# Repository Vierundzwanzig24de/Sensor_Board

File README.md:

# Sensor Board V1

## Platine in Betrieb nehmen:
1. Keine Fuses einlöten, reverse polarity testen (Q1201)
	- Q1201 Pin 3 liegt Versorgungsspannung an
	- V_IN LED (D1210) leuchtet
	- F_Vdrive einlöten, Vdrive LED (D1206) leuchtet
2. Buck converter:
	- F_BUCK (F1201) einlöten
	- U1201 Pin 1 liegen 6V an
	- U1202 Pin 2 liegen 5V an
	- U1203 Pin 2 liegen 5V an
3. LDOs:
	- F_5VA, F_5V und F_3V3 nacheinander einlöten und Ausgänge testen
	- 5VA, 5V und 3.3V LEDs leuchten auf
	- Versorgung wegnehmen und F_USB einlöten
	- USB Versorgung anschließen
	- V_IN, Vdrive und 5VA LEDs bleiben aus, 5V und 3.3V leuchten
	- USB Jumper links setzen (Pins 2+3), 5VA LED leuchtet
	- Spannung an U1203 Pin 2 ist ~0V
	- USB Jumper alle Pins verbinden
	- Spannung an U1202 Pin 2 ist ~0V
	- Eingangsspannung verbinden, V_IN und Vdrive leuchten, Stromverbrauch normal
	- Spannung über D1204 und D1205 messen, danach USB Jumper rechts setzen (Pins 1+2)
	- USB Versorgung trennen, Ausgangsspannung U1202 vergleichen zwischen USB und ohne -> D1204 überbrücken? Wenn ja, Jumper USB nur noch wechseln zwischen 1/2 und 2/3
4. STM32:
	- ST-Link verbinden und Testprogramm aufspielen
	- STATUS LED blinkt
	- Versorgungsspannung wegnehmen
	- USB Versorgung verbinden und erneut Testprogramm aufspielen
	- STATUS LED blinkt immer noch
	
## Prüfen:
- 74HC595 Ausgangsspannung an PU/PD Widerständen!
- Flankensteilheit Halbbrücken einstellen

## Für V2:
- Halbbrücken näher an Stecker (Halbbrücken, 1A-Profets, Buck converter)
- STM um 90° drehen
- USB Stecker weiter herausstehen lassen
- kleinere Gehäuse für ICs nutzen
- Level shifter für 74HC595 nicht notwendig
- 3.3V Outputs??
- Umschalten Ausgangsspannung per Software
- Umschalten USB Versorgung per Software?? (Falls keine Eingangsspannung messbar)
- CAN schaltbare Terminierung
- Vierundzwanzig24 Logo!!!
- AMPSEAL um 0.8mm (0.7mm?) nach innen verschieben

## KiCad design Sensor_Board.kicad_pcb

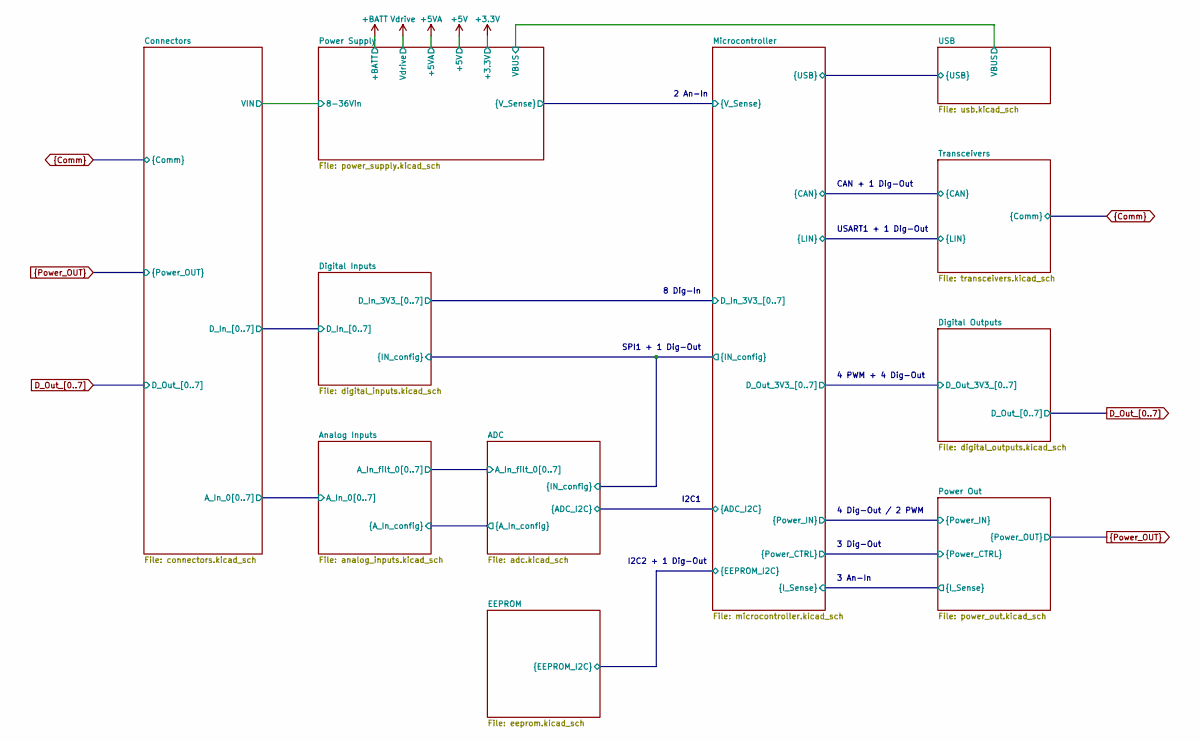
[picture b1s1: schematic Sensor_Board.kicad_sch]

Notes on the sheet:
I2C1
SPI1 + 1 Dig-Out
3 An-In
CAN + 1 Dig-Out
4 Dig-Out / 2 PWM
USART1 + 1 Dig-Out
I2C2 + 1 Dig-Out
3 Dig-Out
4 PWM + 4 Dig-Out
8 Dig-In
2 An-In

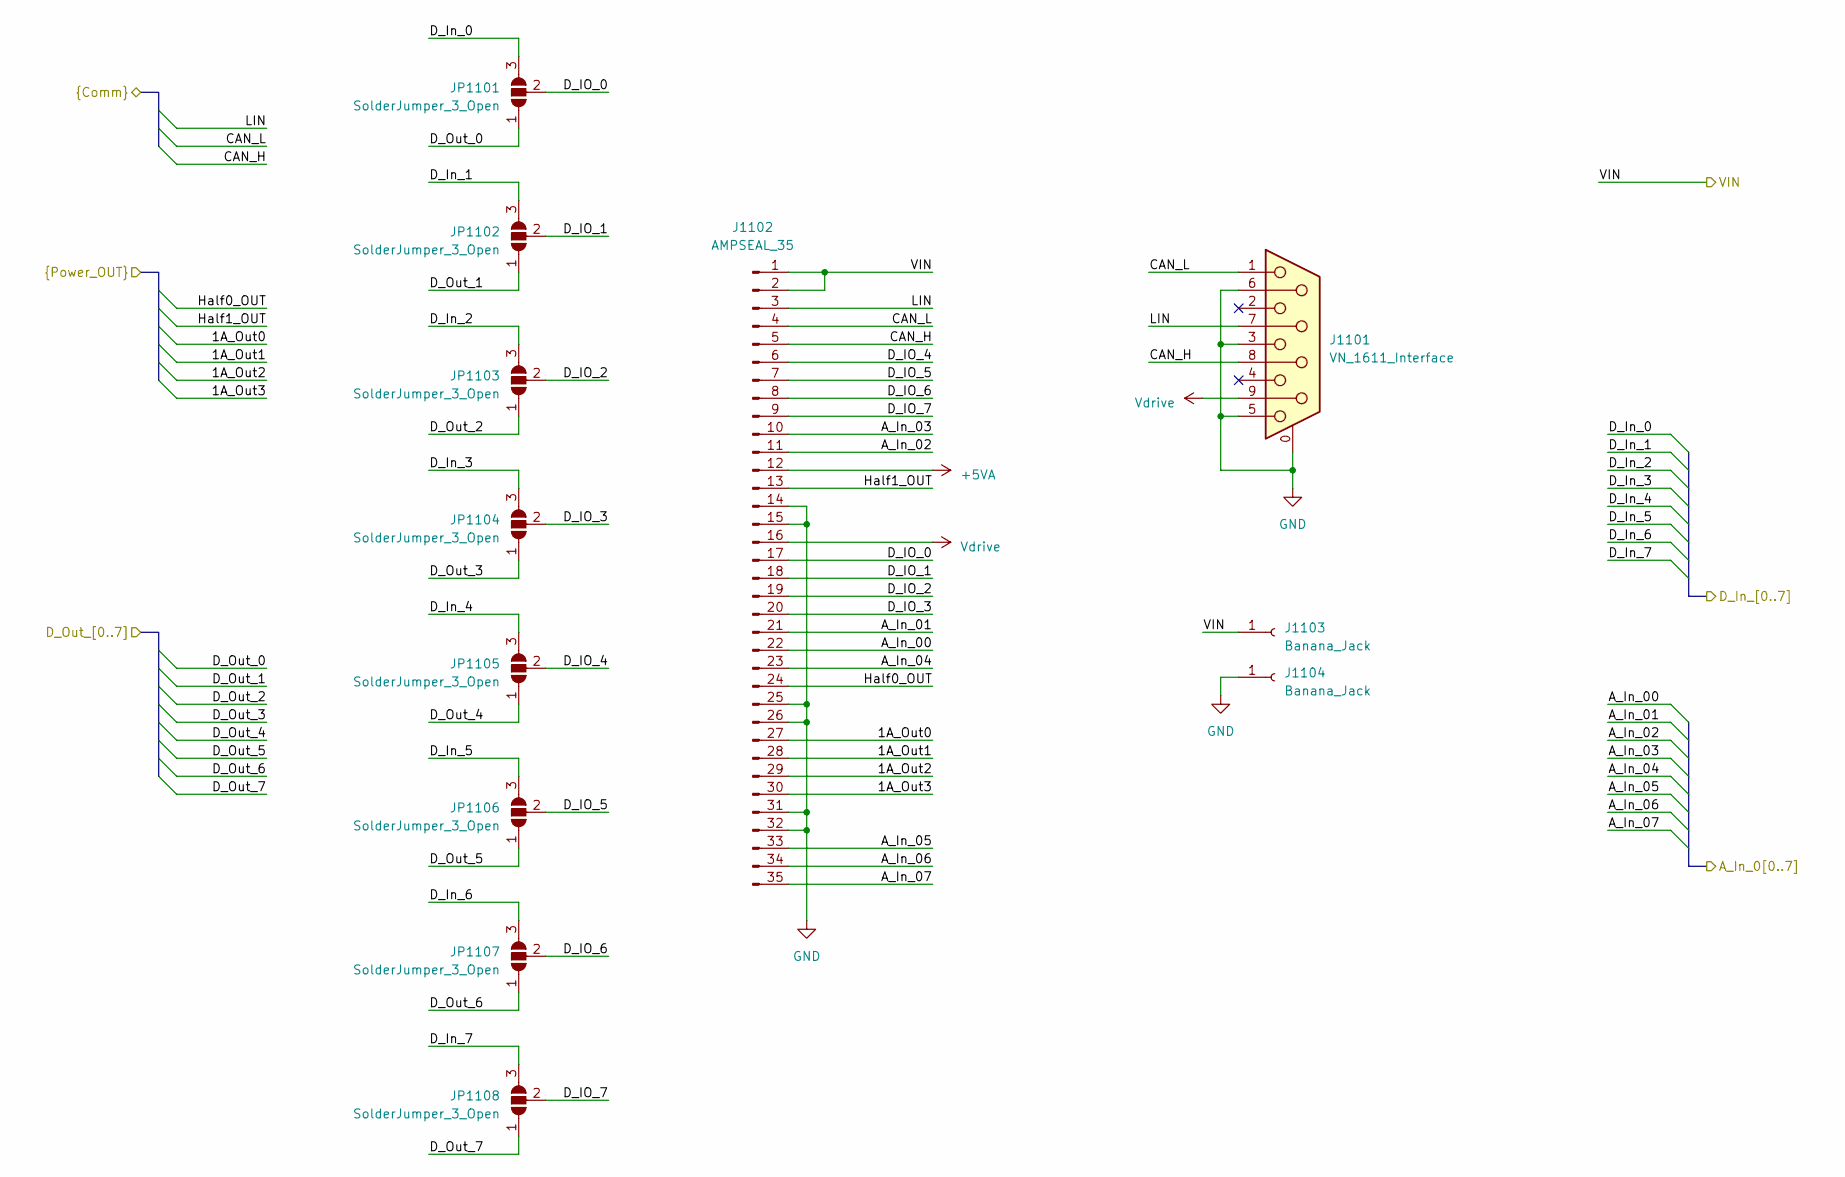
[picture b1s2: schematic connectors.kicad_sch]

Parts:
J1101: VN_1611_Interface; DSUB-9_Female_Horizontal_P2.77x2.84mm_EdgePinOffset9.90mm_H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
J1102: AMPSEAL_35
J1103, J1104: Banana_Jack; Banana_Cliff_FCR7350x_S16N-PC_Horizontal
JP1101, JP1102, JP1103, JP1104, JP1105, JP1106, JP1107, JP1108: SolderJumper_3_Open; SolderJumper-3_P1.3mm_Open_Pad1.0x1.5mm

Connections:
1A_Out1: J1102.28; also elsewhere on the board
1A_Out2: J1102.29; also elsewhere on the board
+5VA: J1102.12; also elsewhere on the board
/Analog Inputs/A_In_00: J1102.22; also elsewhere on the board
/Analog Inputs/A_In_01: J1102.21; also elsewhere on the board
/Analog Inputs/A_In_02: J1102.11; also elsewhere on the board
/Analog Inputs/A_In_03: J1102.10; also elsewhere on the board
/Analog Inputs/A_In_04: J1102.23; also elsewhere on the board
/Analog Inputs/A_In_05: J1102.33; also elsewhere on the board
/Analog Inputs/A_In_06: J1102.34; also elsewhere on the board
/Analog Inputs/A_In_07: J1102.35; also elsewhere on the board
/Connectors/D_IO_0: J1102.17, JP1101.2 (C)
/Connectors/D_IO_1: J1102.18, JP1102.2 (C)
/Connectors/D_IO_2: J1102.19, JP1103.2 (C)
/Connectors/D_IO_3: J1102.20, JP1104.2 (C)
/Connectors/D_IO_4: J1102.6, JP1105.2 (C)
/Connectors/D_IO_5: J1102.7, JP1106.2 (C)
/Connectors/D_IO_6: J1102.8, JP1107.2 (C)
/Connectors/D_IO_7: J1102.9, JP1108.2 (C)
/Connectors/D_In_0: JP1101.3 (B); also elsewhere on the board
/Connectors/D_In_1: JP1102.3 (B); also elsewhere on the board
/Connectors/D_In_2: JP1103.3 (B); also elsewhere on the board
/Connectors/D_In_3: JP1104.3 (B); also elsewhere on the board
/Connectors/D_In_4: JP1105.3 (B); also elsewhere on the board
/Connectors/D_In_5: JP1106.3 (B); also elsewhere on the board
/Connectors/D_In_6: JP1107.3 (B); also elsewhere on the board
/Connectors/D_In_7: JP1108.3 (B); also elsewhere on the board
/Connectors/VIN: J1102.1, J1102.2, J1103.1; also elsewhere on the board
CAN_H: J1101.8, J1102.5; also elsewhere on the board
CAN_L: J1101.1, J1102.4; also elsewhere on the board
D_Out_0: JP1101.1 (A); also elsewhere on the board
D_Out_1: JP1102.1 (A); also elsewhere on the board
D_Out_2: JP1103.1 (A); also elsewhere on the board
D_Out_3: JP1104.1 (A); also elsewhere on the board
D_Out_4: JP1105.1 (A); also elsewhere on the board
D_Out_5: JP1106.1 (A); also elsewhere on the board
D_Out_6: JP1107.1 (A); also elsewhere on the board
D_Out_7: JP1108.1 (A); also elsewhere on the board
Half0_OUT: J1102.24; also elsewhere on the board
Half1_OUT: J1102.13; also elsewhere on the board
LIN: J1101.7, J1102.3; also elsewhere on the board

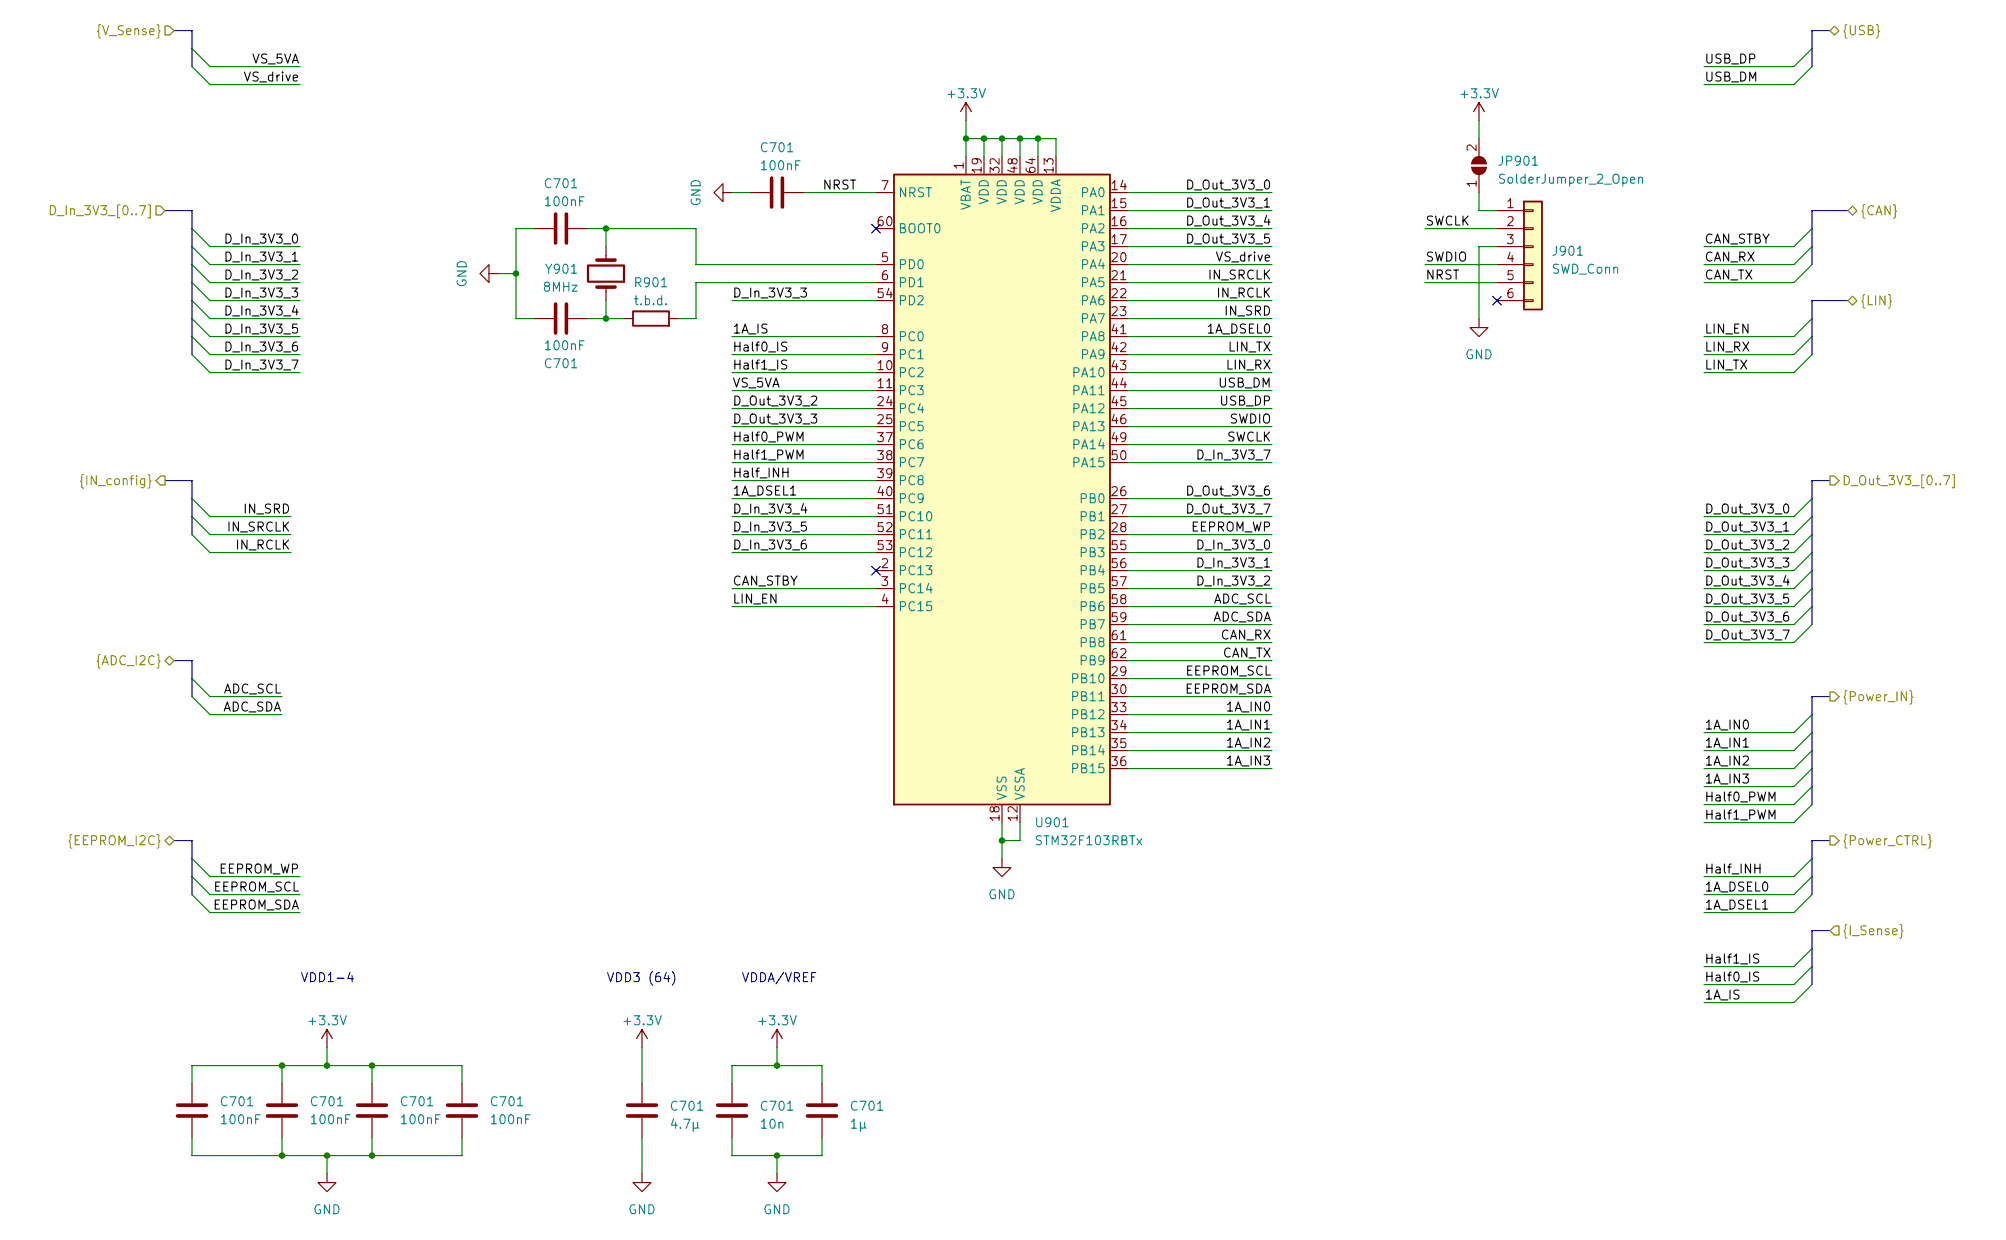
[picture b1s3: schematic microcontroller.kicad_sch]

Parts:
C701: 100nF; C_0603_1608Metric
J901: SWD_Conn; PinHeader_1x06_P2.54mm_Vertical
JP901: SolderJumper_2_Open; SolderJumper-2_P1.3mm_Open_Pad1.0x1.5mm
R901: t.b.d.; R_0603_1608Metric
U901: STM32F103RBTx; LQFP-64_10x10mm_P0.5mm
Y901: 8MHz; Crystal_SMD_3225-4Pin_3.2x2.5mm

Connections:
/ADC/ADC_SCL: U901.58 (PB6); also elsewhere on the board
/ADC/ADC_SDA: U901.59 (PB7); also elsewhere on the board
/ADC/IN_RCLK: U901.22 (PA6); also elsewhere on the board
/ADC/IN_SRCLK: U901.21 (PA5); also elsewhere on the board
/ADC/IN_SRD: U901.23 (PA7); also elsewhere on the board
/Digital Inputs/D_In_3V3_0: U901.55 (PB3); also elsewhere on the board
/Digital Inputs/D_In_3V3_1: U901.56 (PB4); also elsewhere on the board
/Digital Inputs/D_In_3V3_2: U901.57 (PB5); also elsewhere on the board
/Digital Inputs/D_In_3V3_3: U901.54 (PD2); also elsewhere on the board
/Digital Inputs/D_In_3V3_4: U901.51 (PC10); also elsewhere on the board
/Digital Inputs/D_In_3V3_5: U901.52 (PC11); also elsewhere on the board
/Digital Inputs/D_In_3V3_6: U901.53 (PC12); also elsewhere on the board
/Digital Inputs/D_In_3V3_7: U901.50 (PA15); also elsewhere on the board
/Digital Outputs/D_Out_3V3_0: U901.14 (PA0); also elsewhere on the board
/Digital Outputs/D_Out_3V3_1: U901.15 (PA1); also elsewhere on the board
/Digital Outputs/D_Out_3V3_2: U901.24 (PC4); also elsewhere on the board
/Digital Outputs/D_Out_3V3_3: U901.25 (PC5); also elsewhere on the board
/Digital Outputs/D_Out_3V3_4: U901.16 (PA2); also elsewhere on the board
/Digital Outputs/D_Out_3V3_5: U901.17 (PA3); also elsewhere on the board
/Digital Outputs/D_Out_3V3_6: U901.26 (PB0); also elsewhere on the board
/Digital Outputs/D_Out_3V3_7: U901.27 (PB1); also elsewhere on the board
/EEPROM/EEPROM_SCL: U901.29 (PB10); also elsewhere on the board
/EEPROM/EEPROM_SDA: U901.30 (PB11); also elsewhere on the board
/EEPROM/EEPROM_WP: U901.28 (PB2); also elsewhere on the board
/Microcontroller/1A_DSEL0: U901.41 (PA8); also elsewhere on the board
/Microcontroller/1A_DSEL1: U901.40 (PC9); also elsewhere on the board
/Microcontroller/1A_IN0: U901.33 (PB12); also elsewhere on the board
/Microcontroller/1A_IN1: U901.34 (PB13); also elsewhere on the board
/Microcontroller/1A_IN2: U901.35 (PB14); also elsewhere on the board
/Microcontroller/1A_IN3: U901.36 (PB15); also elsewhere on the board
/Microcontroller/1A_IS: U901.8 (PC0); also elsewhere on the board
/Microcontroller/CAN_RX: U901.61 (PB8); also elsewhere on the board
/Microcontroller/CAN_STBY: U901.3 (PC14); also elsewhere on the board
/Microcontroller/CAN_TX: U901.62 (PB9); also elsewhere on the board
/Microcontroller/Half0_IS: U901.9 (PC1); also elsewhere on the board
/Microcontroller/Half0_PWM: U901.37 (PC6); also elsewhere on the board
/Microcontroller/Half1_IS: U901.10 (PC2); also elsewhere on the board
/Microcontroller/Half1_PWM: U901.38 (PC7); also elsewhere on the board
/Microcontroller/Half_INH: U901.39 (PC8); also elsewhere on the board
/Microcontroller/LIN_EN: U901.4 (PC15); also elsewhere on the board
/Microcontroller/LIN_RX: U901.43 (PA10); also elsewhere on the board
/Microcontroller/LIN_TX: U901.42 (PA9); also elsewhere on the board
/Microcontroller/SWCLK: J901.2, U901.49 (PA14)
/Microcontroller/SWDIO: J901.4, U901.46 (PA13)
/Microcontroller/USB_DM: U901.44 (PA11); also elsewhere on the board
/Microcontroller/USB_DP: U901.45 (PA12); also elsewhere on the board
/Microcontroller/VS_5VA: U901.11 (PC3); also elsewhere on the board
/Microcontroller/VS_drive: U901.20 (PA4); also elsewhere on the board
unnamed: J901.1, JP901.1 (A)
unnamed: R901.2, U901.6 (PD1)

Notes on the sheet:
VDD3 (64)
VDDA/VREF
VDD1-4

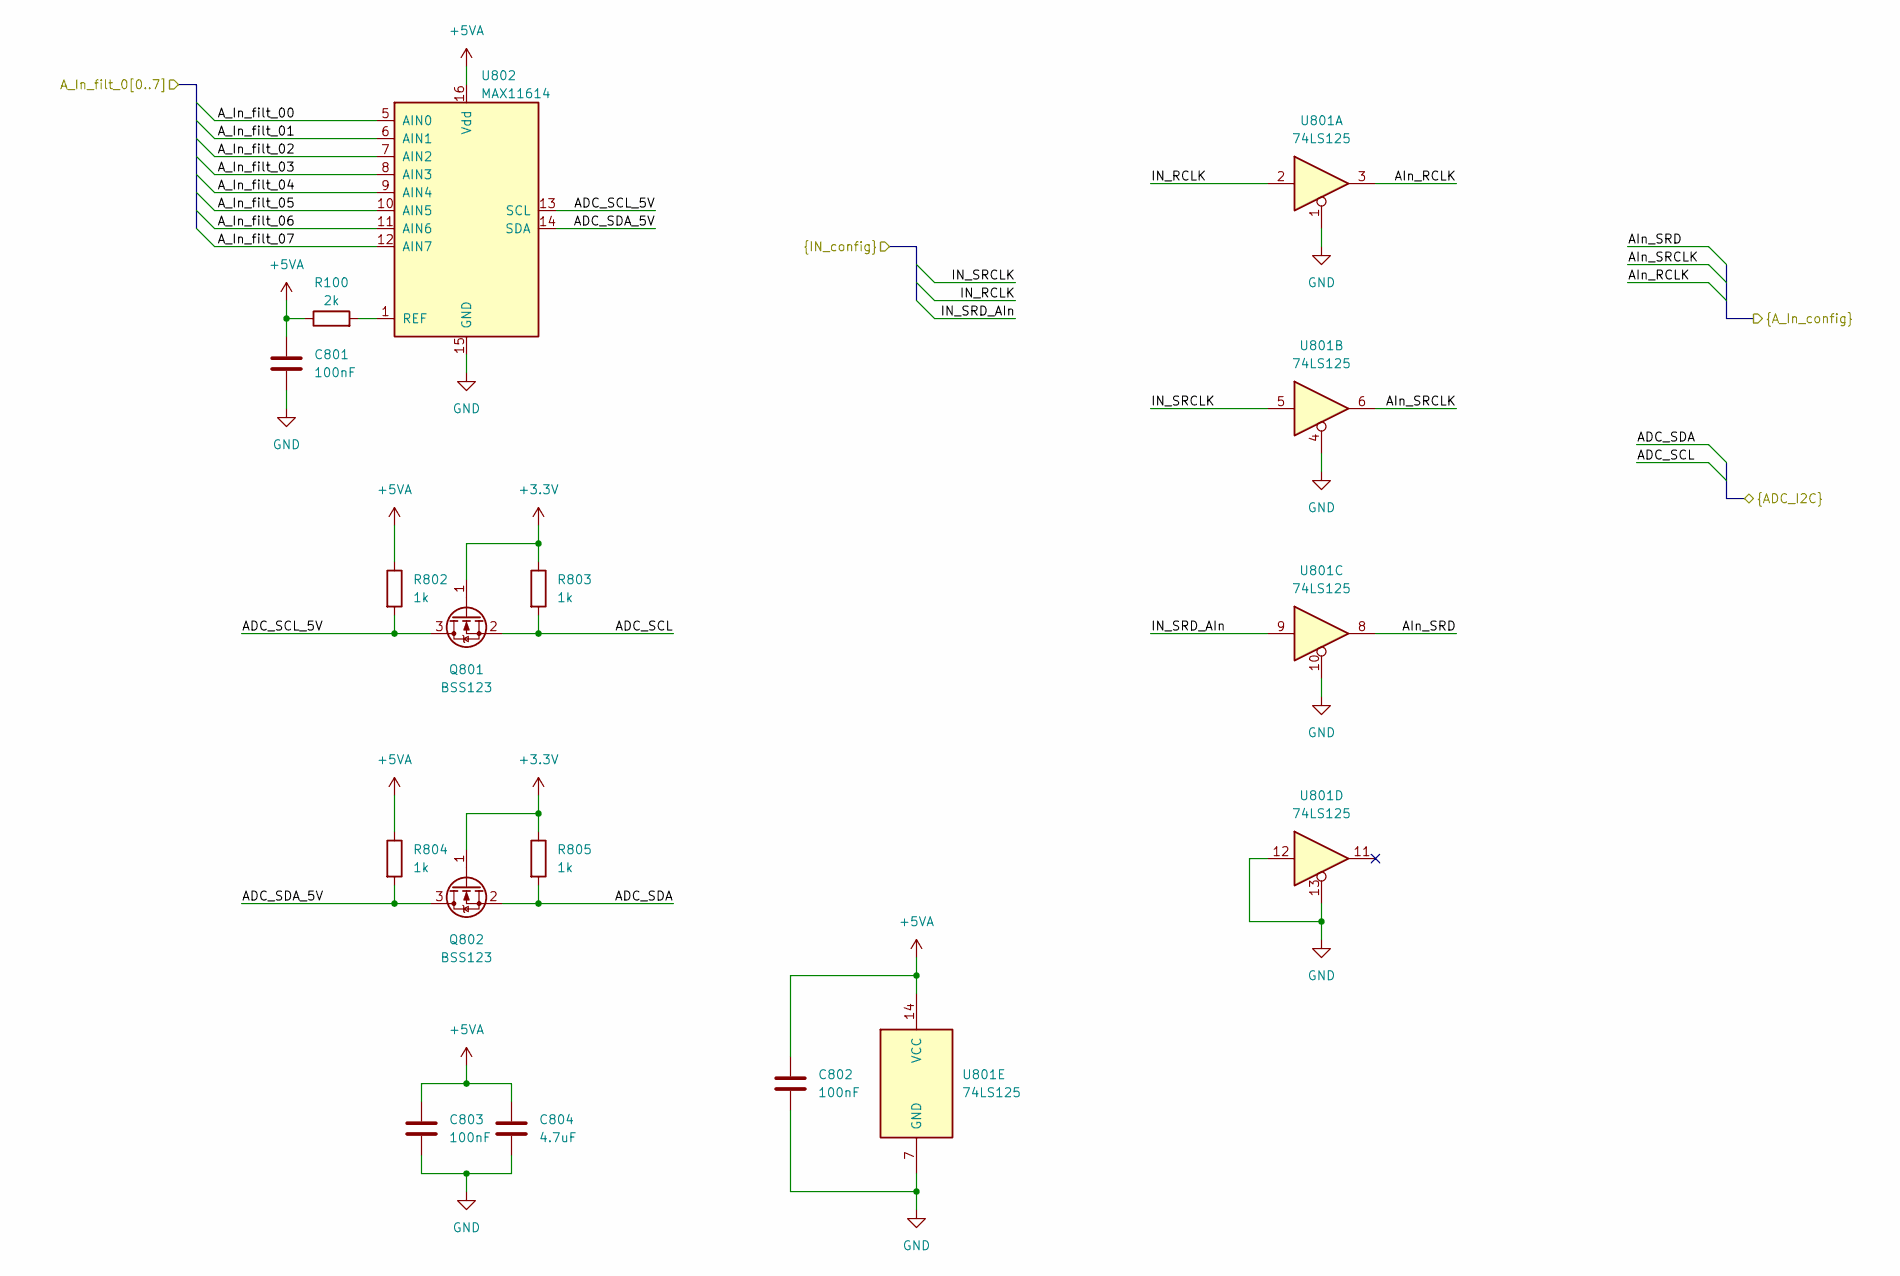
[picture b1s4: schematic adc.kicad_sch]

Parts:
C801, C802, C803: 100nF; C_0603_1608Metric
C804: 4.7uF; C_0805_2012Metric
Q801, Q802: BSS123; SOT-23
R100: 2k; R_0603_1608Metric
R802, R803, R804, R805: 1k; R_0603_1608Metric
U801: 74LS125; SOIC-16_3.9x9.9mm_P1.27mm
U802: MAX11614; QSOP-16_3.9x4.9mm_P0.635mm

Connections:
+5VA: C801.1, C802.1, C803.1, C804.1, R802.1, R804.1, U801.14 (VCC), U802.16 (Vdd); also elsewhere on the board
/ADC/ADC_SCL: Q801.2 (S), R803.2; also elsewhere on the board
/ADC/ADC_SCL_5V: Q801.3 (D), R802.2, U802.13 (SCL)
/ADC/ADC_SDA: Q802.2 (S), R805.2; also elsewhere on the board
/ADC/ADC_SDA_5V: Q802.3 (D), R804.2, U802.14 (SDA)
/ADC/AIn_RCLK: U801.3; also elsewhere on the board
/ADC/AIn_SRCLK: U801.6; also elsewhere on the board
/ADC/AIn_SRD: U801.8; also elsewhere on the board
/ADC/A_In_filt_00: U802.5 (AIN0); also elsewhere on the board
/ADC/A_In_filt_01: U802.6 (AIN1); also elsewhere on the board
/ADC/A_In_filt_02: U802.7 (AIN2); also elsewhere on the board
/ADC/A_In_filt_03: U802.8 (AIN3); also elsewhere on the board
/ADC/A_In_filt_04: U802.9 (AIN4); also elsewhere on the board
/ADC/A_In_filt_05: U802.10 (AIN5); also elsewhere on the board
/ADC/A_In_filt_06: U802.11 (AIN6); also elsewhere on the board
/ADC/A_In_filt_07: U802.12 (AIN7); also elsewhere on the board
/ADC/IN_RCLK: U801.2; also elsewhere on the board
/ADC/IN_SRCLK: U801.5; also elsewhere on the board
/ADC/IN_SRD_AIn: U801.9; also elsewhere on the board
unnamed 245: U802.1 (REF); also elsewhere on the board

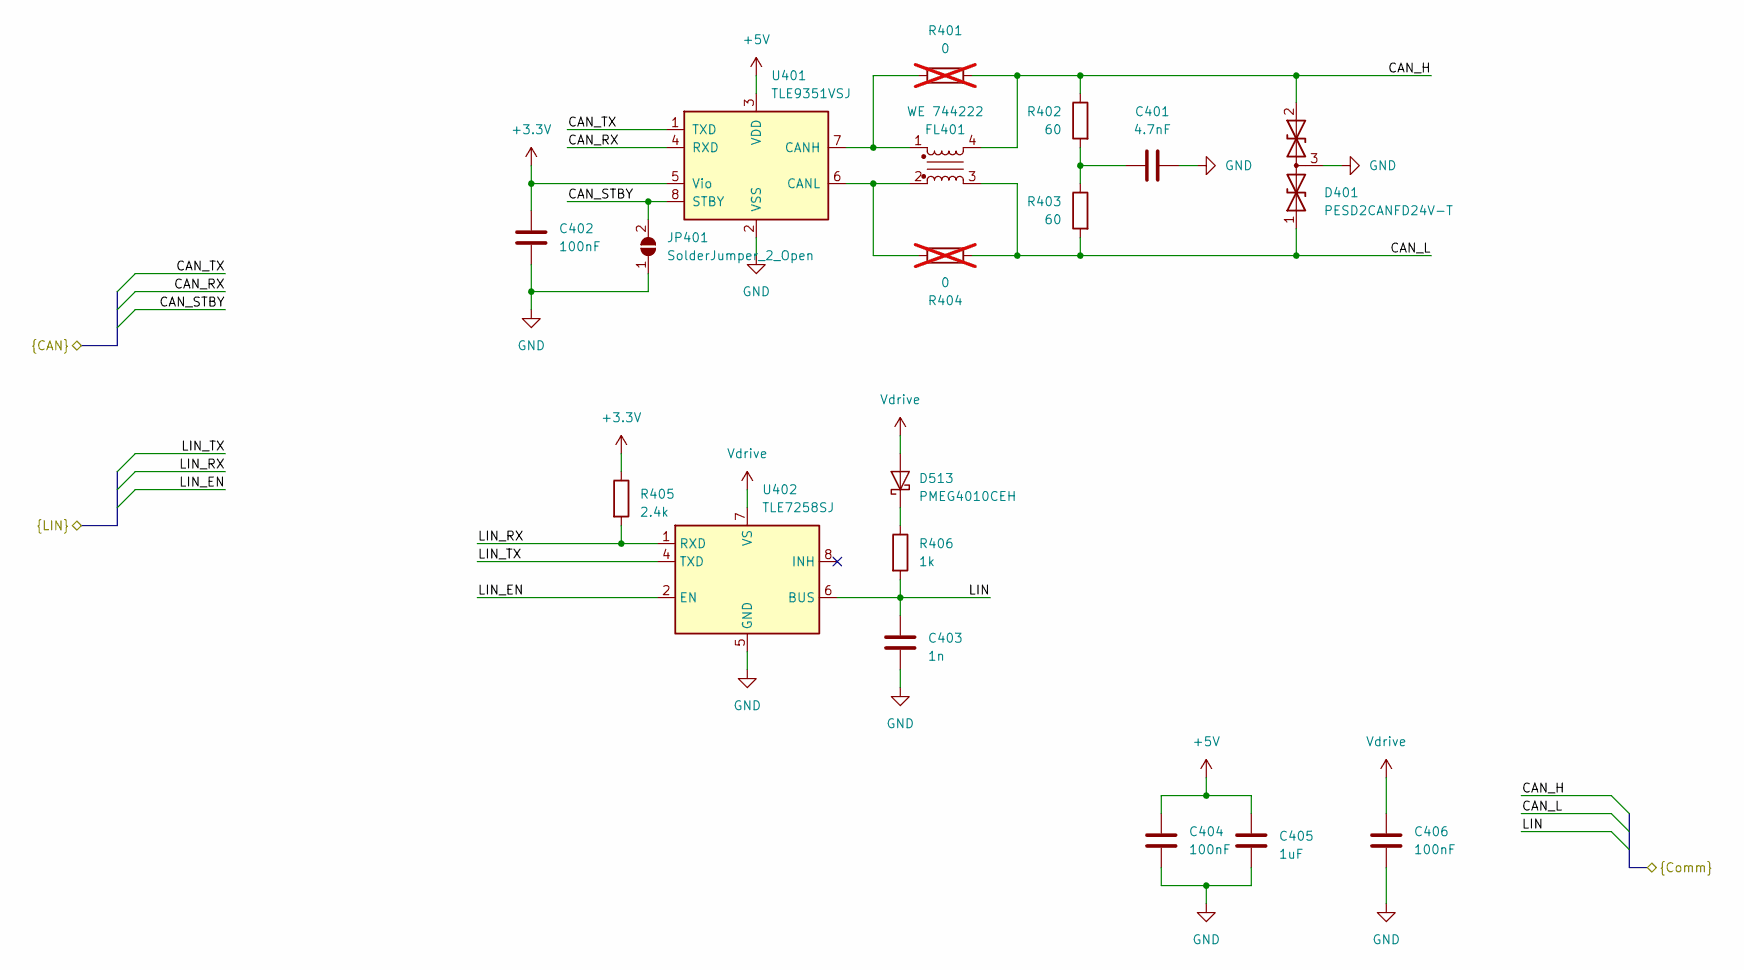
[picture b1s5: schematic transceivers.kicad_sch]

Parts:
C401: 4.7nF; C_0603_1608Metric
C402, C404, C406: 100nF; C_0603_1608Metric
C403: 1n; C_0603_1608Metric
C405: 1uF; C_0603_1608Metric
D401: PESD2CANFD24V-T; SOT-23-3
D513: PMEG4010CEH; D_SOD-123F
FL401: WE 744222; L_CommonMode_Wuerth_WE-SL2
JP401: SolderJumper_2_Open; SolderJumper-2_P1.3mm_Open_Pad1.0x1.5mm
R401, R404: 0; R_0603_1608Metric; not fitted
R402, R403: 60; R_0603_1608Metric
R405: 2.4k; R_0603_1608Metric
R406: 1k; R_1206_3216Metric
U401: TLE9351VSJ; SOIC-8_3.9x4.9mm_P1.27mm
U402: TLE7258SJ; SOIC-8_3.9x4.9mm_P1.27mm

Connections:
+5V: C404.1, C405.1, U401.3 (VDD); also elsewhere on the board
/Microcontroller/CAN_RX: U401.4 (RXD); also elsewhere on the board
/Microcontroller/CAN_STBY: JP401.2 (B), U401.8 (STBY); also elsewhere on the board
/Microcontroller/CAN_TX: U401.1 (TXD); also elsewhere on the board
/Microcontroller/LIN_EN: U402.2 (EN); also elsewhere on the board
/Microcontroller/LIN_RX: R405.2, U402.1 (RXD); also elsewhere on the board
/Microcontroller/LIN_TX: U402.4 (TXD); also elsewhere on the board
CAN_H: D401.2 (A2), FL401.4, R401.2, R402.1; also elsewhere on the board
CAN_L: D401.1 (A1), FL401.3, R403.2, R404.2; also elsewhere on the board
LIN: C403.1, R406.2, U402.6 (BUS); also elsewhere on the board
unnamed: C401.1, R402.2, R403.1
unnamed: FL401.1, R401.1, U401.7 (CANH)
unnamed: FL401.2, R404.1, U401.6 (CANL)

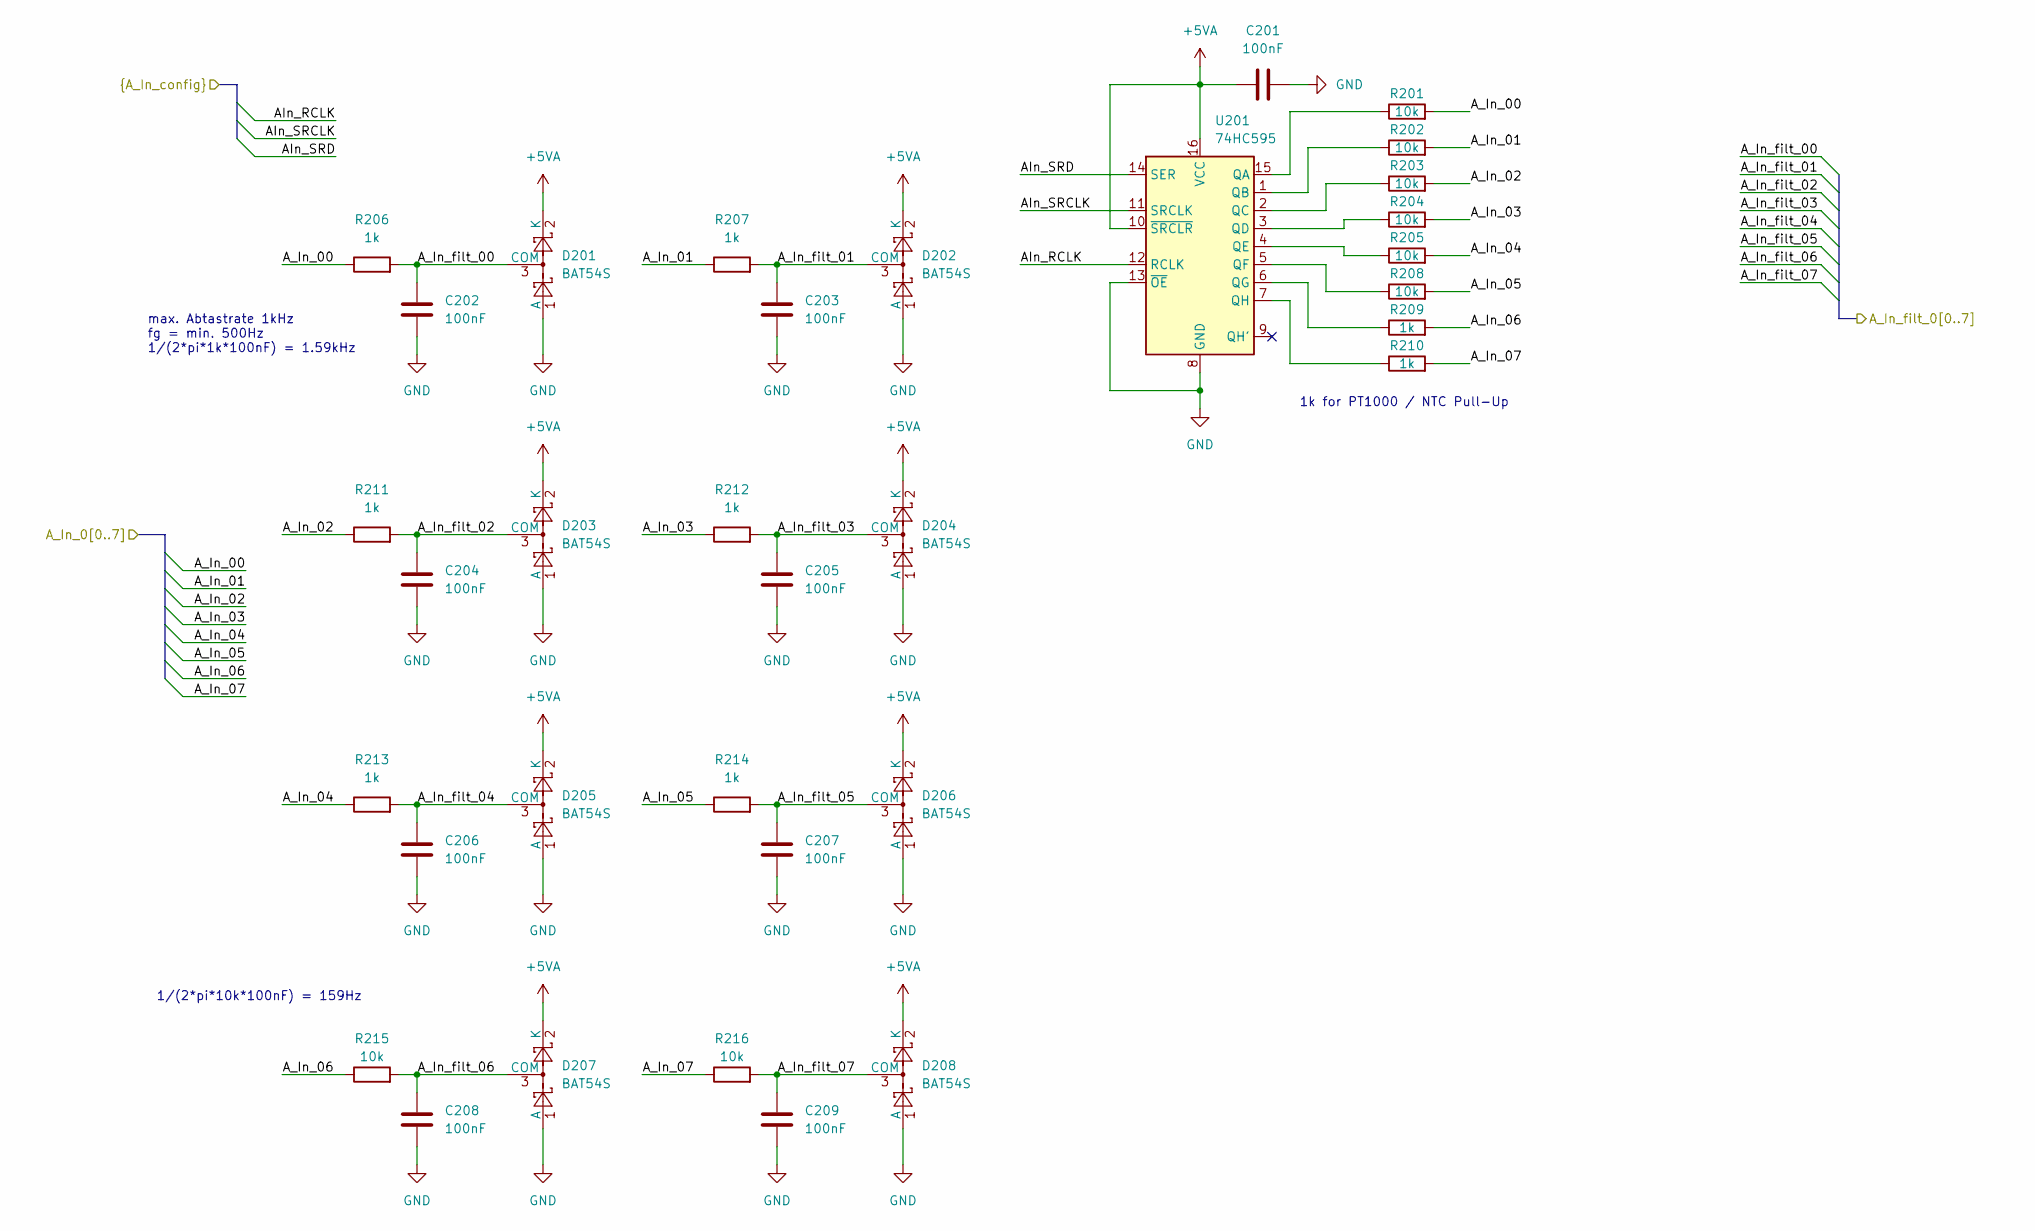
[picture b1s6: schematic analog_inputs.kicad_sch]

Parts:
C201, C202, C203, C204, C205, C206, C207, C208, C209: 100nF; C_0603_1608Metric
D201, D202, D203, D204, D205, D206, D207, D208: BAT54S; SOT-23
R201, R202, R203, R204, R205, R208, R215, R216: 10k; R_0603_1608Metric
R206, R207, R209, R210, R211, R212, R213, R214: 1k; R_0603_1608Metric
U201: 74HC595; SOIC-16_3.9x9.9mm_P1.27mm

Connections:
+5VA: C201.1, D201.2 (K), D202.2 (K), D203.2 (K), D204.2 (K), D205.2 (K), D206.2 (K), D207.2 (K), D208.2 (K), U201.10 (~SRCLR), U201.16 (VCC); also elsewhere on the board
/ADC/AIn_RCLK: U201.12 (RCLK); also elsewhere on the board
/ADC/AIn_SRCLK: U201.11 (SRCLK); also elsewhere on the board
/ADC/AIn_SRD: U201.14 (SER); also elsewhere on the board
/ADC/A_In_filt_00: C202.1, D201.3 (COM), R206.2; also elsewhere on the board
/ADC/A_In_filt_01: C203.1, D202.3 (COM), R207.2; also elsewhere on the board
/ADC/A_In_filt_02: C204.1, D203.3 (COM), R211.2; also elsewhere on the board
/ADC/A_In_filt_03: C205.1, D204.3 (COM), R212.2; also elsewhere on the board
/ADC/A_In_filt_04: C206.1, D205.3 (COM), R213.2; also elsewhere on the board
/ADC/A_In_filt_05: C207.1, D206.3 (COM), R214.2; also elsewhere on the board
/ADC/A_In_filt_06: C208.1, D207.3 (COM), R215.2; also elsewhere on the board
/ADC/A_In_filt_07: C209.1, D208.3 (COM), R216.2; also elsewhere on the board
/Analog Inputs/A_In_00: R201.2, R206.1; also elsewhere on the board
/Analog Inputs/A_In_01: R202.2, R207.1; also elsewhere on the board
/Analog Inputs/A_In_02: R203.2, R211.1; also elsewhere on the board
/Analog Inputs/A_In_03: R204.2, R212.1; also elsewhere on the board
/Analog Inputs/A_In_04: R205.2, R213.1; also elsewhere on the board
/Analog Inputs/A_In_05: R208.2, R214.1; also elsewhere on the board
/Analog Inputs/A_In_06: R209.2, R215.1; also elsewhere on the board
/Analog Inputs/A_In_07: R210.2, R216.1; also elsewhere on the board
unnamed: R201.1, U201.15 (QA)
unnamed: R202.1, U201.1 (QB)
unnamed: R203.1, U201.2 (QC)
unnamed: R204.1, U201.3 (QD)
unnamed: R205.1, U201.4 (QE)
unnamed: R208.1, U201.5 (QF)
unnamed: R209.1, U201.6 (QG)
unnamed: R210.1, U201.7 (QH)

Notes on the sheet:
1k for PT1000 / NTC Pull-Up
1/(2*pi*10k*100nF) = 159Hz
max. Abtastrate 1kHz fg = min. 500Hz 1/(2*pi*1k*100nF) = 1.59kHz
